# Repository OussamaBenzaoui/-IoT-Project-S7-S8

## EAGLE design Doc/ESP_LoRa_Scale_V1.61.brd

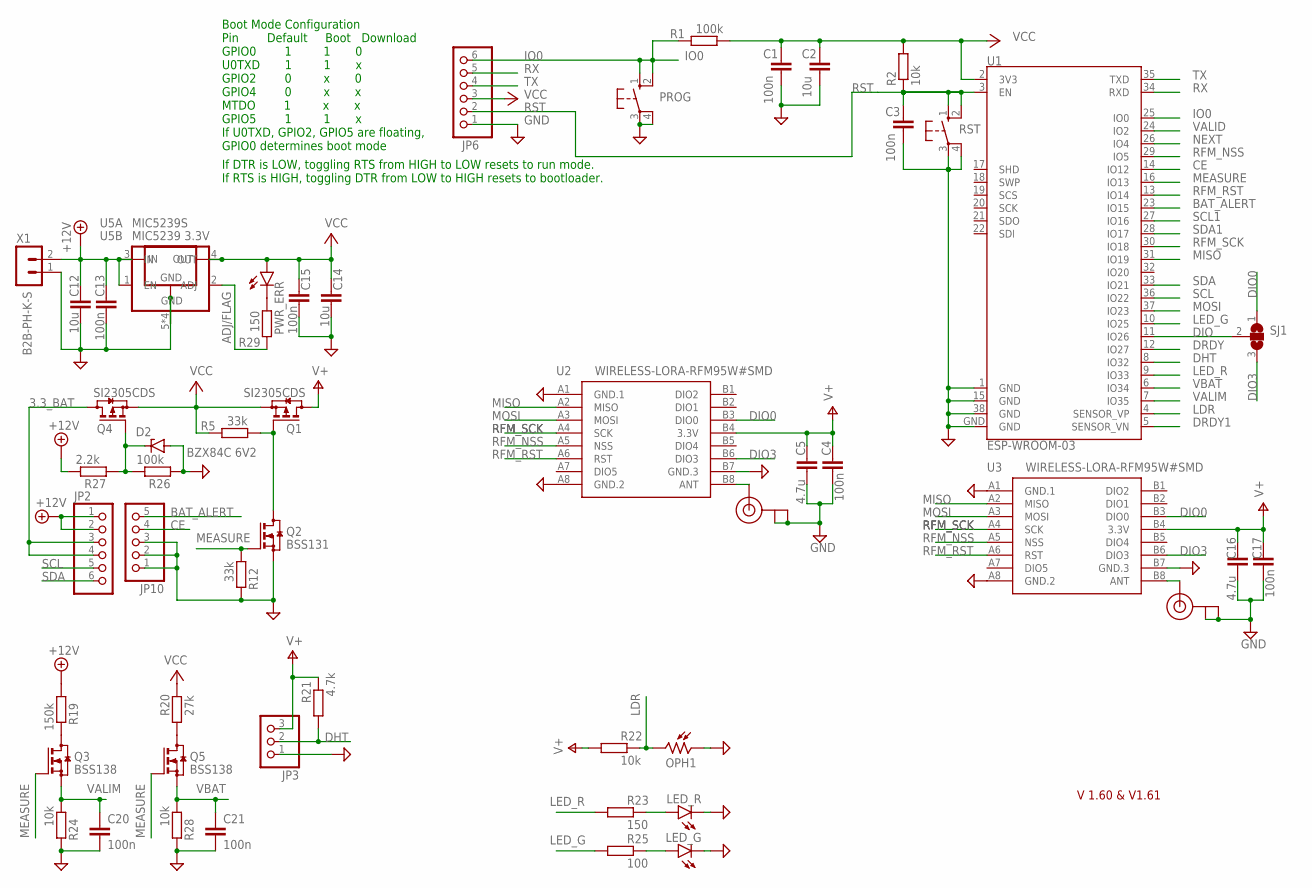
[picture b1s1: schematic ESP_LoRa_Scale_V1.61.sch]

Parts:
C1, C3, C4, C13, C15, C17, C20, C21: 100n; C1206
C2, C12, C14: 10u; C1210
C5, C16: 4.7u; C1210
D2: BZX84C 6V2; TO236
J1, J2: U.FL
JP2, JP6: PINHD-1X6; 1X06
JP3: PINHD-1X3; 1X03
JP10: PINHD-1X5; 1X05
LED_G: LEDSMT1206; 1206
LED_R: LEDSMT1206; 1206
OPH1: VT93N2; VT900
PROG: 10-XX; B3F-10XX
PWR_ERR: LEDSMT1206; 1206
Q1, Q4: SI2305CDS; SOT23
Q2: BSS131; SOT23
Q3, Q5: BSS138; SOT23
R1, R26: 100k; R1206
R2, R22, R24, R28: 10k; R1206
R5, R12: 33k; R1206
R19: 150k; R1206
R20: 27k; R1206
R21: 4.7k; R1206
R23, R29: 150; R1206
R25: 100; R1206
R27: 2.2k; R1206
RST: 10-XX; B3F-10XX
SJ1: SJ2W; SJ_2
U1: ESP-WROOM-03
U2, U3: WIRELESS-LORA-RFM95W#SMD
U5A: MIC5239 3.3V; MSOP08
U5B: MIC5239S; SOT223
X1: B2B-PH-K-S

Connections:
3.3_BAT: JP2.3, JP2.4, Q4.3 (D)
+12V: C12.1, C13.1, JP2.1, JP2.2, R19.1, R27.2, U5A.1 (EN), U5A.3 (IN), U5B.1 (IN), X1.2
ADJ/FLAG: R29.2, U5A.2 (ADJ)
ANT: J1.3 (SIGNAL), U3.B8 (ANT)
ANT2: J2.3 (SIGNAL), U2.B8 (ANT)
BAT_ALERT: JP10.5, U1.23 (IO15)
CE: JP10.4, U1.14 (IO12)
DHT: JP3.2, R21.1, U1.8 (IO32)
DIO: SJ1.2, U1.11 (IO26)
DIO0: SJ1.1, U2.B3 (DIO0), U3.B3 (DIO0)
DIO3: SJ1.3, U2.B6 (DIO3), U3.B6 (DIO3)
DRDY: U1.12 (IO27)
DRDY1: U1.5 (SENSOR_VN)
GND: C1.2, C2.2, C3.2, C4.2, C5.2, C12.2, C13.2, C14.2, C15.2, C16.2, C17.2, C20.2, C21.2, D2.A, J1.1 (GND), J1.2 (GND), J2.1 (GND), J2.2 (GND), JP3.1, JP6.1, JP10.1, JP10.2, JP10.3, LED_G.C, LED_R.C, OPH1.1, PROG.3, PROG.4 (P1), Q2.2 (S), R12.2, R24.2, R26.1, R28.2, RST.3, RST.4 (P1), U1.1 (GND), U1.15 (GND), U1.38 (GND), U1.GND, U2.A1 (GND.1), U2.A8 (GND.2), U2.B7 (GND.3), U3.A1 (GND.1), U3.A8 (GND.2), U3.B7 (GND.3), U5A.5 (GND), U5A.6 (GND), U5A.7 (GND), U5A.8 (GND), U5B.2 (GND), U5B.4 (GND), X1.1
IO0: JP6.6, PROG.1 (S), PROG.2 (S1), R1.2, U1.25 (IO0)
LDR: OPH1.2, R22.2, U1.4 (SENSOR_VP)
LED_G: R25.1, U1.10 (IO25)
LED_R: R23.1, U1.9 (IO33)
MEASURE: Q2.1 (G), Q3.1 (G), Q5.1 (G), R12.1, U1.16 (IO13)
MISO: U1.31 (IO19), U2.A2 (MISO), U3.A2 (MISO)
MOSI: U1.37 (IO23), U2.A3 (MOSI), U3.A3 (MOSI)
unnamed: Q1.1 (G), Q2.3 (D), R5.1
unnamed: Q3.3 (D), R19.2
unnamed: Q5.3 (D), R20.1
unnamed: PWR_ERR.C, R29.1
unnamed: LED_R.A, R23.2
unnamed: LED_G.A, R25.2
unnamed: D2.C, Q4.1 (G), R26.2, R27.1
NEXT: U1.26 (IO4)
RFM_NSS: U1.29 (IO5), U2.A5 (NSS), U3.A5 (NSS)
RFM_RST: U1.13 (IO14), U2.A6 (RST), U3.A6 (RST)
RFM_SCK: U1.30 (IO18), U2.A4 (SCK), U3.A4 (SCK)
RST: C3.1, JP6.2, R2.1, RST.1 (S), RST.2 (S1), U1.3 (EN)
RX: JP6.5, U1.34 (RXD)
SCL: JP2.5, U1.36 (IO22)
SCL1: U1.27 (IO16)
SDA: JP2.6, U1.33 (IO21)
SDA1: U1.28 (IO17)
TX: JP6.4, U1.35 (TXD)
V+: C4.1, C5.1, C16.1, C17.1, JP3.3, Q1.3 (D), R21.2, R22.1, U2.B4 (3.3V), U3.B4 (3.3V)
VALID: U1.24 (IO2)
VALIM: C20.1, Q3.2 (S), R24.1, U1.7 (IO35)
VBAT: C21.1, Q5.2 (S), R28.1, U1.6 (IO34)
VCC: C1.1, C2.1, C14.1, C15.1, JP6.3, PWR_ERR.A, Q1.2 (S), Q4.2 (S), R1.1, R2.2, R5.2, R20.2, U1.2 (3V3), U5A.4 (OUT), U5B.3 (OUT)

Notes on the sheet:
If DTR is LOW, toggling RTS from HIGH to LOW resets to run mode. If RTS is HIGH, toggling DTR from LOW to HIGH resets to bootloader.
Boot Mode Configuration Pin Default Boot Download GPIO0 1 1 0 U0TXD 1 1 x GPIO2 0 x 0 GPIO4 0 x x MTDO 1 x x GPIO5 1 1 x If U0TXD, GPIO2, GPIO5 are floating, GPIO0 determines boot mode
V 1.60 & V1.61

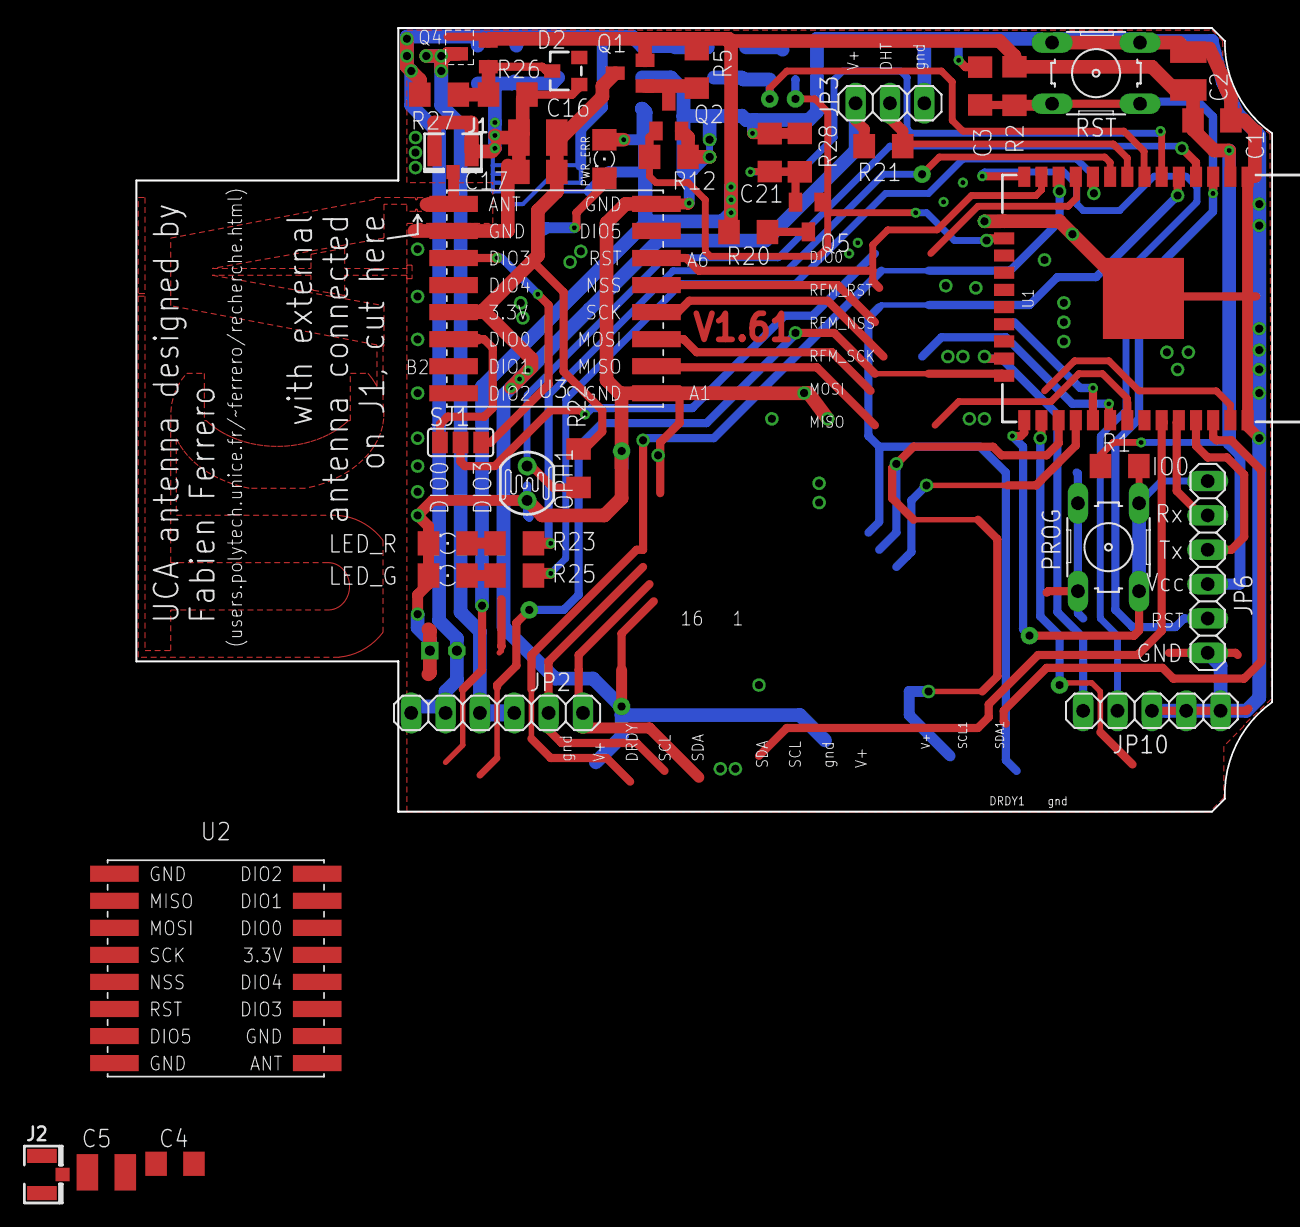
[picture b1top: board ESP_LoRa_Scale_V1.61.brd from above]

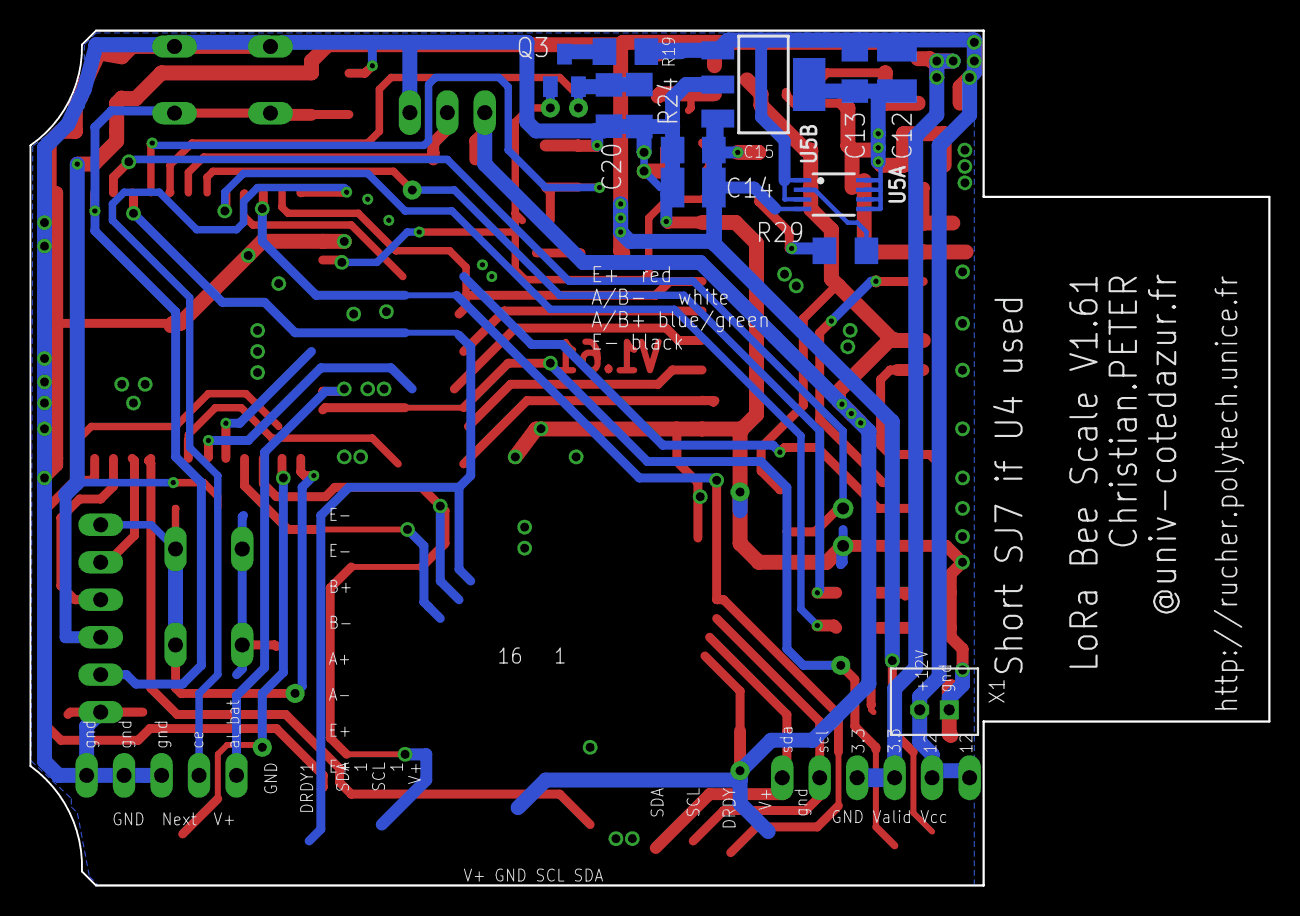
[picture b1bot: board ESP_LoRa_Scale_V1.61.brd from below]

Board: 2 copper layers, 84.0 x 57.9 mm, 53 parts (12 on the bottom side), 38 nets.

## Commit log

2022-12-01 Create Third hand to solder CMS components
2022-12-01 Create SX126x_Receive
2022-12-01 Create RSSI
2022-12-01 Create red
2022-12-01 Create Energy_metering
2022-12-20 Update Energy_metering
2022-12-20 Create edit
2023-01-19 Create Sleep_test
2023-03-16 Create pinout

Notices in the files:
parts and their libraries:
diy-modules: Released under the Creative Commons Attribution 4.0 International License: http://creativecommons.org/licenses/by/4.0
micrel: Copyright (C) 2008, Bob Starr
